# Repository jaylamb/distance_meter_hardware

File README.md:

# Distance Meter Hardware

The distance meter hardware project consists of a single printed circuit board (PCB) which
houses connectors for the hardware. A list of the hardware is available below. The PCB is
designed to be fastened within a project box.

Each piece of attached hardware is a complete built-up unit, and requires no supporting
circuitry.

Software deployed to this hardware is located
[here](https://github.com/jaylamb/distance_meter.git).

## Required hardware:
* 1x Adafruit Metro Mini (ATMEGA328P)
* 1x MaxBotix LV-MaxSonar-EZ SONAR range finder
* 1x Adafruit 0.96" monochrome 128x64 OLED graphic display
* 1x CircuitSetup 3.94" x 2.375" 1.875" project box
* 4x 7-position female header (PPPC071LFBN-RC)
* 2x 14-position female header (PPPC141LFBN-RC)

## Usage
Project schematic and PCB layout files are available for reference. Project Gerbers can be
used to manufacture the hardware itself.

## License [Apache 2.0](http://www.apache.org/licenses/)

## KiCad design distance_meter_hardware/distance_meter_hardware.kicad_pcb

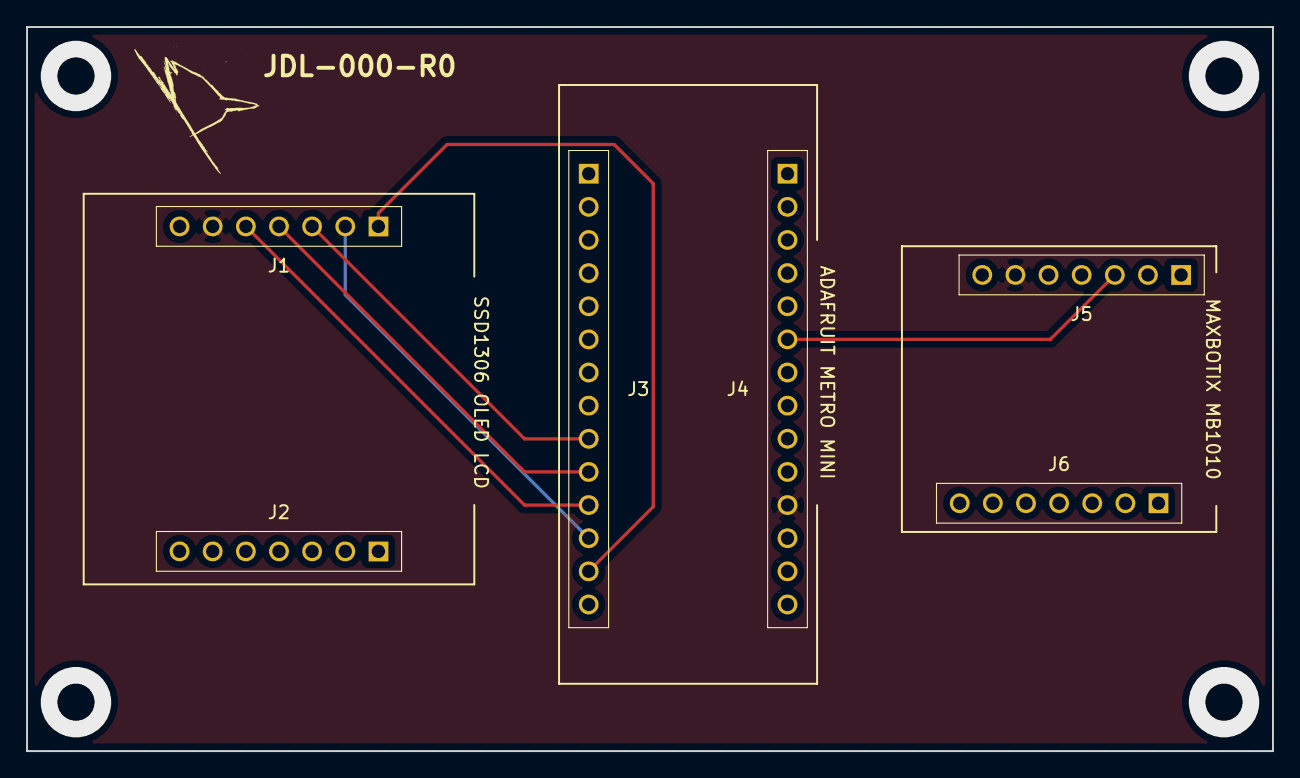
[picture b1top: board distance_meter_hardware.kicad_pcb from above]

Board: 2 copper layers, 95.5 x 55.5 mm, 6 parts (0 on the bottom side), 8 nets.

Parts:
J1, J2, J5, J6: PPPC071LFBN-RC
J3, J4: PPPC141LFBN-RC

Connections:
+5V: J1.6, J4.11, J5.6
GND: J1.7, J4.10, J5.7
unnamed: J1.1, J3.13
unnamed: J1.2, J3.12
unnamed: J1.3, J3.9
unnamed: J1.4, J3.10
unnamed: J1.5, J3.11
unnamed: J4.6, J5.3

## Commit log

2019-12-08 Initial commit.
    Add CHANGELOG, README, and LICENCE to project.
2019-12-25 Add Kicad project to project
2019-12-26 Add components to schematic
2019-12-26 Add netlist to project
2020-01-04 Organize components and silk in layout
2020-01-05 Resize layout to fit in project box
2020-01-05 Add routes to schematic. Update netlist
2020-01-05 Add routing to PCB layout
2020-01-06 Correct routing
2020-01-06 Add generated Gerber files to project
2020-01-12 Add logo to PCB layout. Move measures to user-defined layer
2020-01-12 Add project information to schematic sheet. Re-annotate schematic.
2020-01-12 Add PCB render to project repository
2020-12-12 Add symbol and footprint library tables to project.
2020-12-12 Update design to work with footprint and symbol submodules
    Add personal symbols and footprints project as submodule.
    Add KiCad official symbols repository as submodule.
    Add Git ignore rules.
